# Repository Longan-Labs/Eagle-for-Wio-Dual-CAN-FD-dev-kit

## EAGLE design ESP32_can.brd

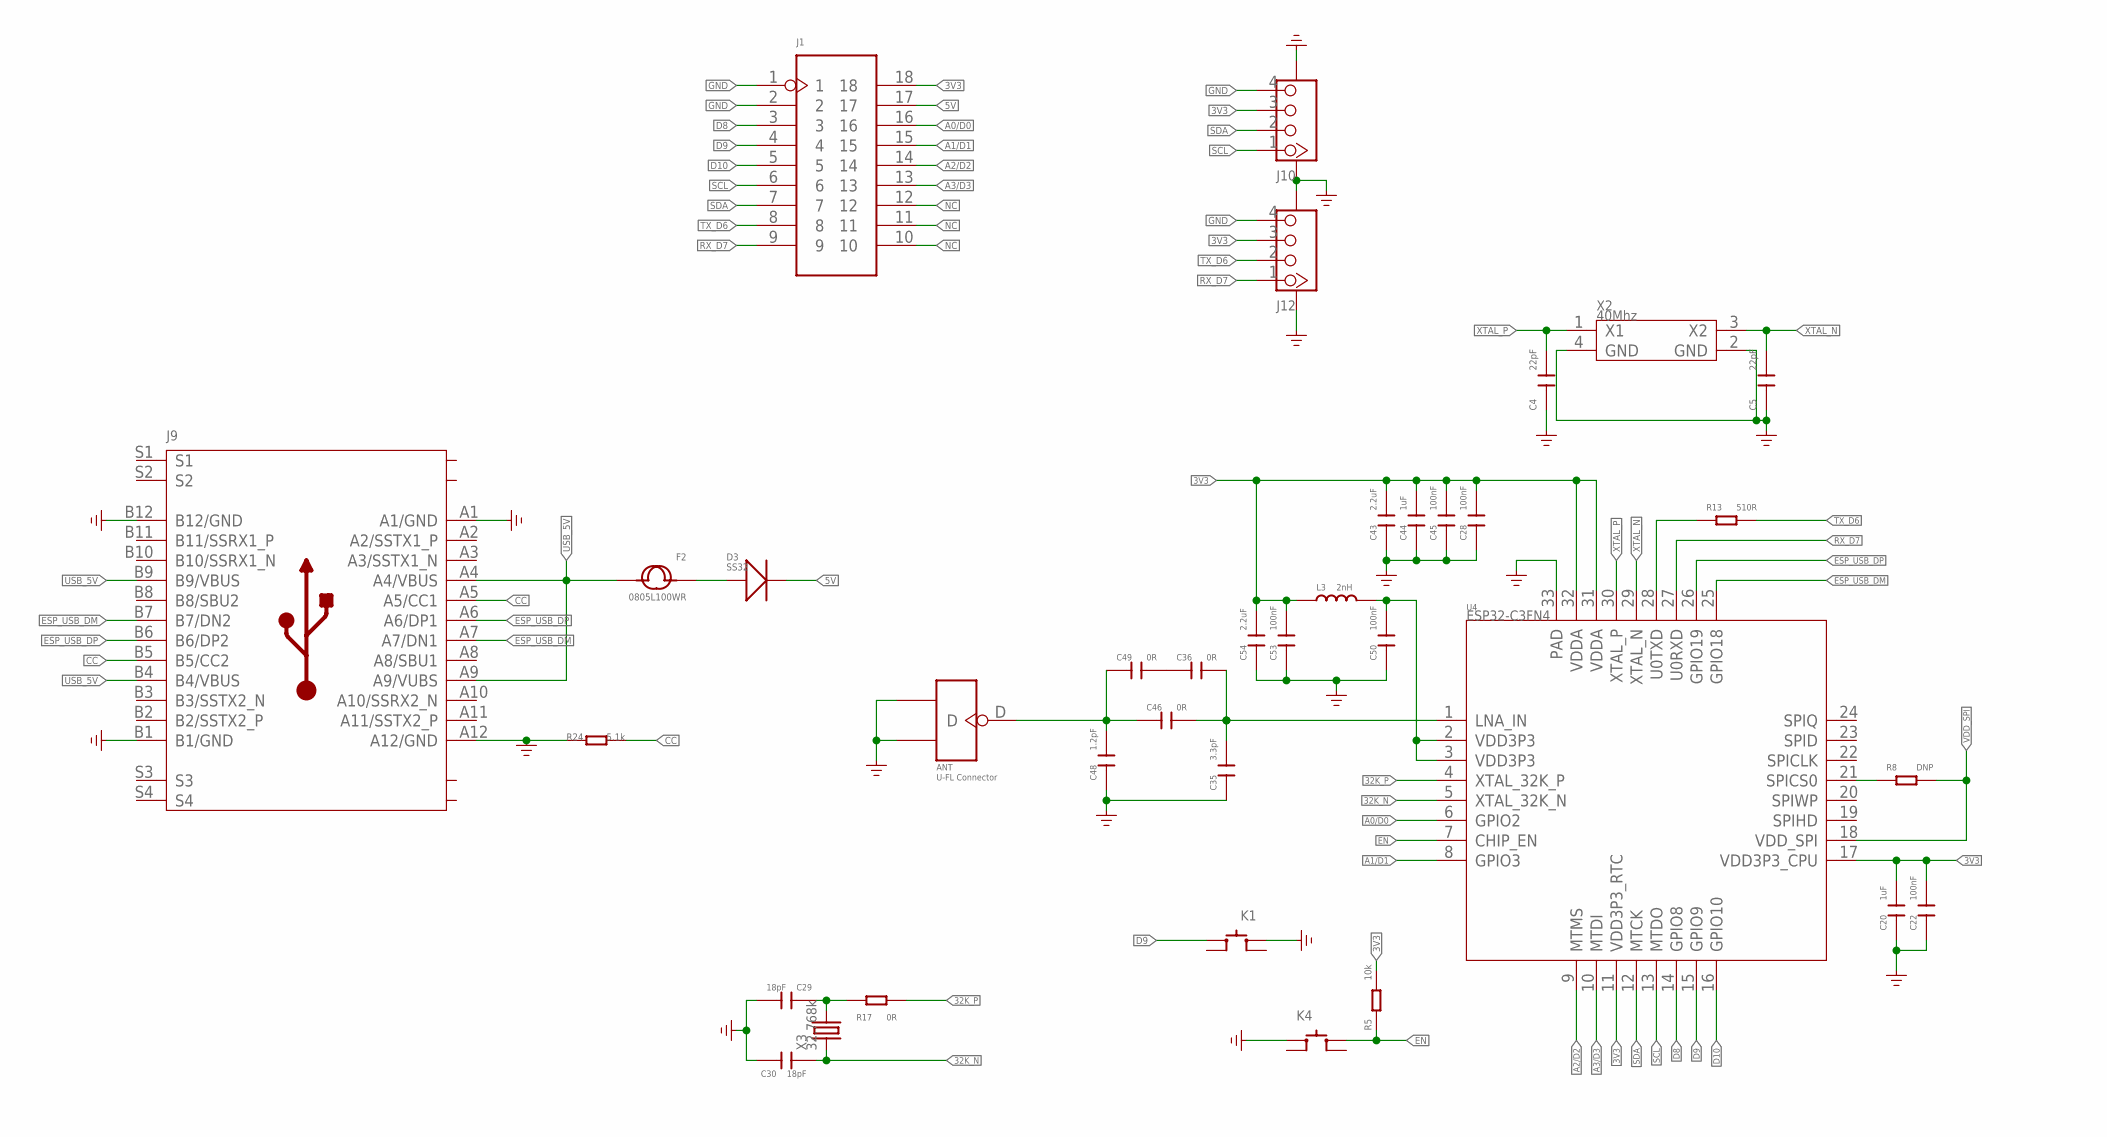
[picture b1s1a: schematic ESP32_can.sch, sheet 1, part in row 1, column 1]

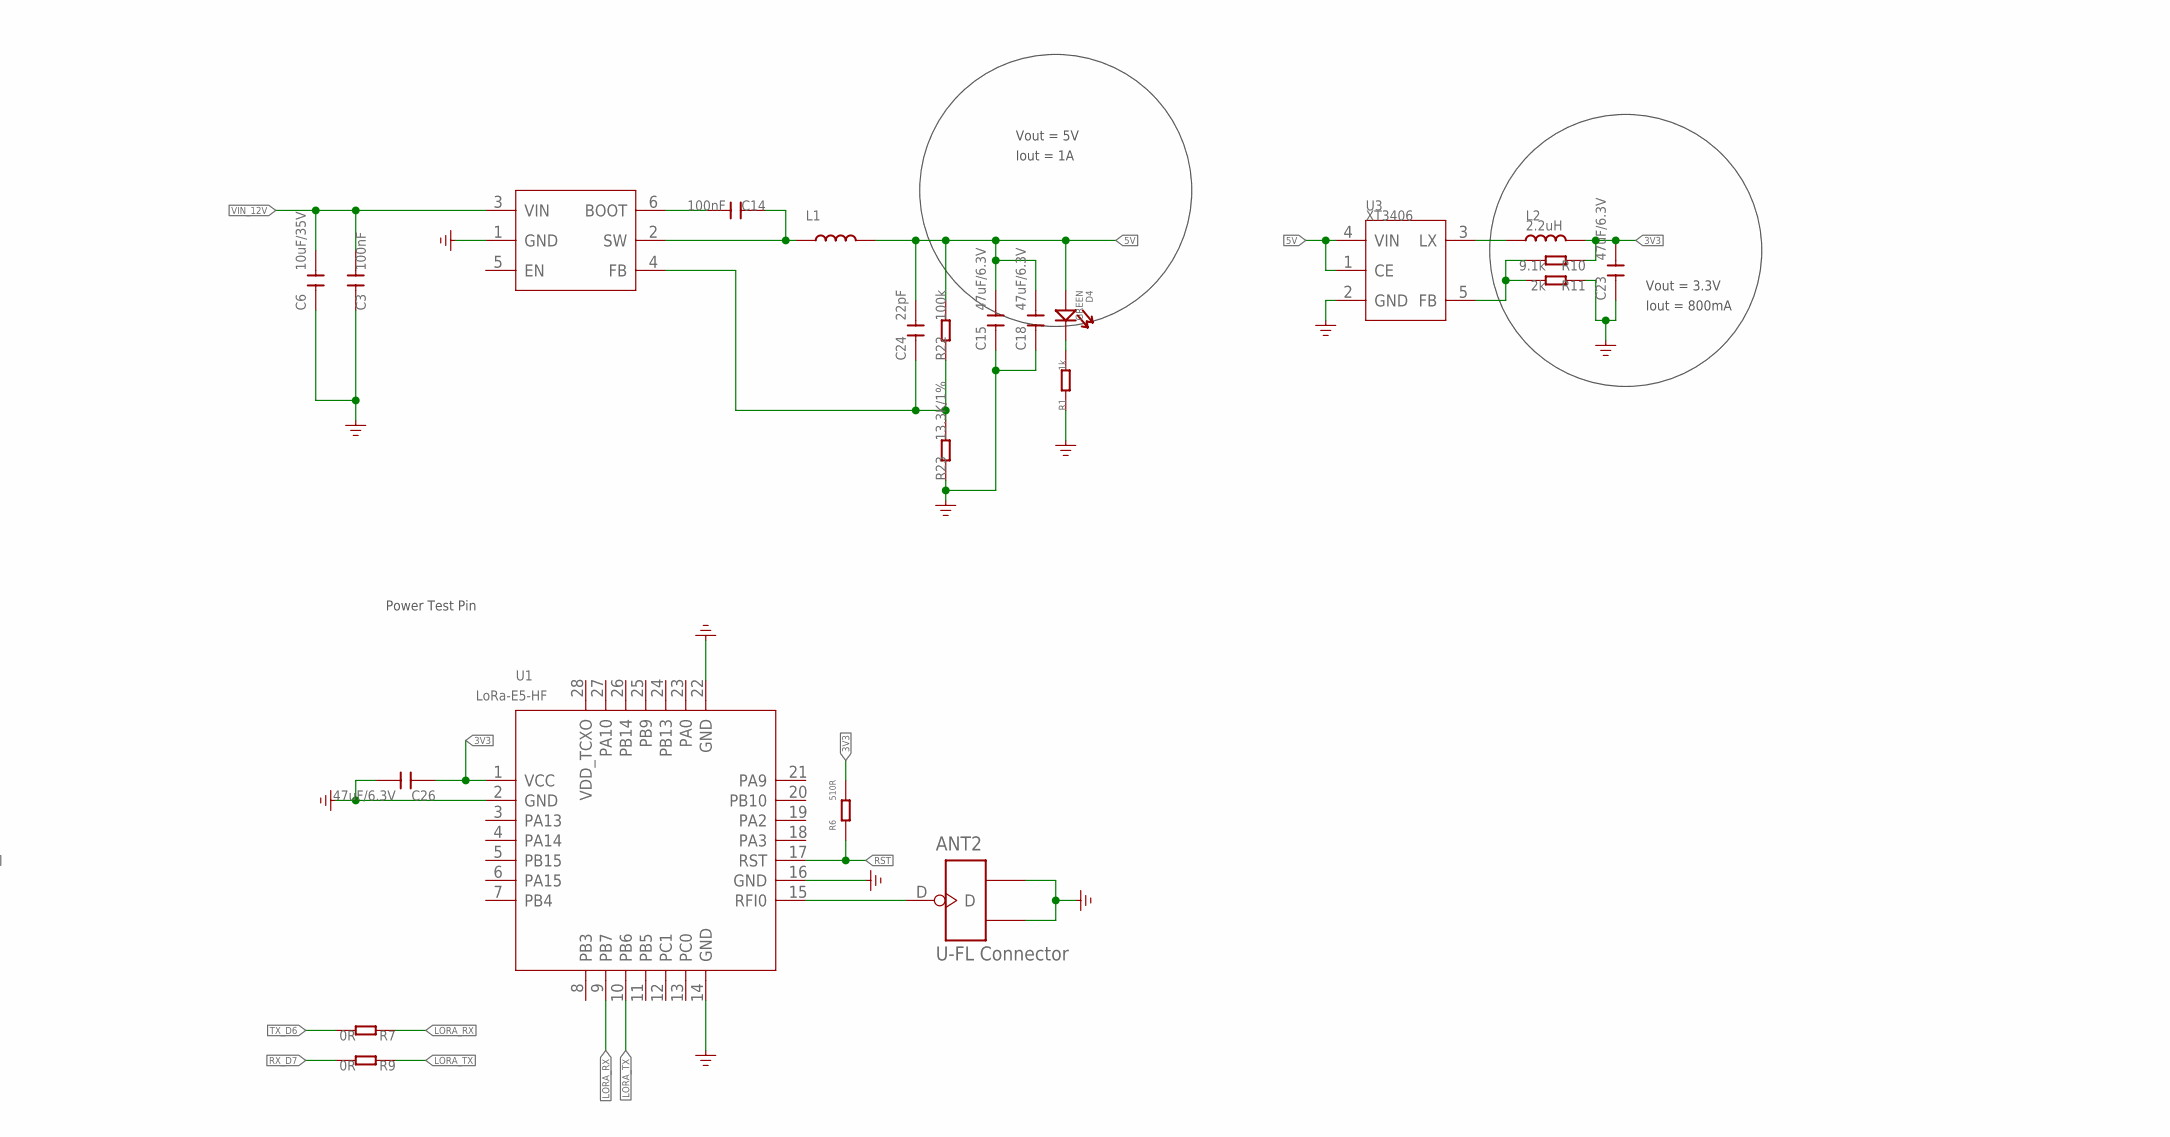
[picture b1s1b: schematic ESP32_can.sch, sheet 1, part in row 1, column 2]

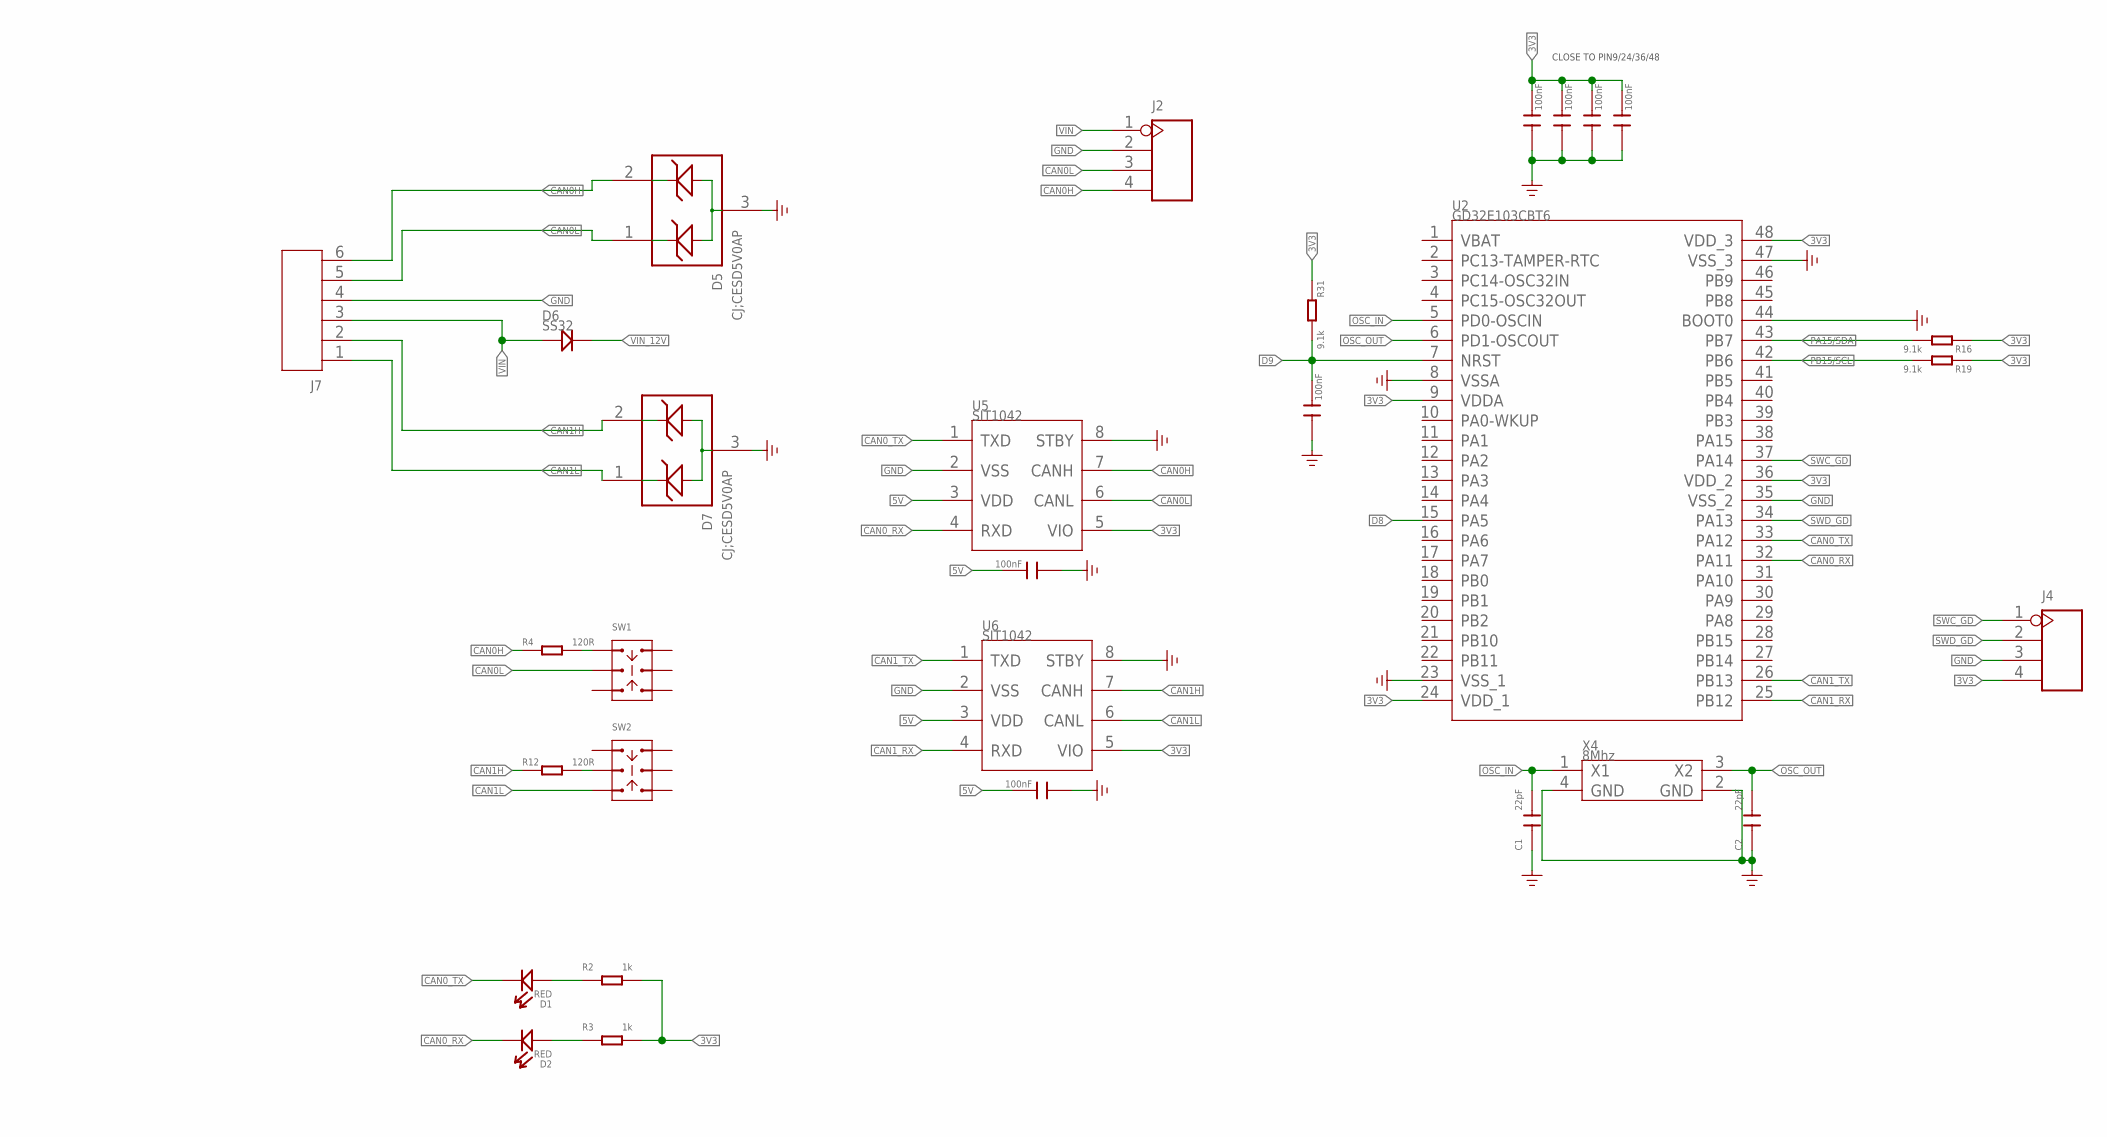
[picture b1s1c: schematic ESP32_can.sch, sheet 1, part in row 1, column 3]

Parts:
ANT, ANT2: U-FL Connector; U-FL3P-SMD-2.6X2.6X1.0MM
C1, C2, C4, C5, C24: 22pF; C0603
C3, C7, C8, C9, C10, C14, C16, C17, C19, C22, C28, C45, C50, C53: 100nF; C0603
C6: 10uF/35V; C1206
C15, C18, C23, C26: 47uF/6.3V; C0805
C20, C44: 1uF; C0603
C29, C30: 18pF; C0603
C35: 3.3pF; C0603
C36, C46, C49: 0R; C0603
C43, C54: 2.2uF; C0603
C48: 1.2pF; C0603
D1, D2: RED; LED-0603
D3: SS32; DO-214AC@2
D4: GREEN; LED-0603
D5, D7: CJ;CESD5V0AP; SOT-23
D6: SS32; DO-214AC
F2: 0805L100WR; F0805
J1: HEADER-2X9P-2.54; H2X9-2.54
J2: HEADER-4P-80/40MIL; H4-2.54-C80D40MIL
J4: HEADER-4P-65/35MIL; H4-2.54
J7: SCREW-TERMINAL-6P-5.0; H6-5.0-31.6X12.5X12MM
J9: USB-TYPE-C-90; TYPE-C-0.5-8.94X3.16X9.2MM
J10, J12: GROVE-CONNECTOR-SMD-320110030; HW4-SMD-2.0
K1, K4: BUTTON-4P-6.2X6.2; SW4-SMD-6.2X6.2MM
L1: INDUCTOR-SPD3D16-4R7M; L0420
L2: 2.2uH; L3030-TAIYO-YUDEN-NR3012
L3: 2nH; L0603
R1, R2, R3: 1k; R0603
R4, R12: 120R; R0603
R5: 10k; R0603
R6, R13: 510R; R0603
R7, R9, R17: 0R; R0603
R8: DNP; R0603
R10, R16, R19, R31: 9.1k; R0603
R11: 2k; R0603
R22: 100k; R0603
R23: 13.3K/1%; R0603
R24: 5.1k; R0603
SW1, SW2: SWITCH-2CH-6P-311010004; SW6-2.54-9.0X3.5X3.2+2.0MM
U1: LoRa-E5-HF; MOUDLE28P-1.25-12X12X2.5MM
U2: GD32E103CBT6; LQFP48
U3: XT3406; SOT-23-5
U4: ESP32-C3FN4; QFN32G-0.5-5X5MM
U5, U6: SIT1042; SOIC8-1.27-5X4MM
U9: PMIC-TPS54302; SOT-23-6
X2: 40Mhz; X4-SMD-3.2X2.5X0.7MM
X3: 32.768k; X2-SMD-1.6X1.0X0.5MM
X4: 8Mhz; X4-SMD-3.2X2.5X0.7MM

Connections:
3V3: C7.2, C9.2, C16.2, C17.2, C20.2, C22.2, C23.2, C26.1, C28.2, C43.2, C44.2, C45.2, C53.2, C54.2, J1.18, J4.4, J10.3, J12.3, L2.2, L3.1, R2.2, R3.2, R5.2, R6.1, R10.1, R16.1, R19.1, R31.1, U1.1 (VCC), U2.9 (VDDA), U2.24 (VDD_1), U2.36 (VDD_2), U2.48 (VDD_3), U4.11 (VDD3P3_RTC), U4.17 (VDD3P3_CPU), U4.31 (VDDA), U4.32 (VDDA), U5.5 (VIO), U6.5 (VIO)
5V: C8.2, C15.2, C18.2, C19.2, C24.2, D3.2 (-), D4.+, J1.17, L1.2, R22.2, U3.1 (CE), U3.4 (VIN), U5.3 (VDD), U6.3 (VDD)
32K_N: C30.1, U4.5 (XTAL_32K_N), X3.1
32K_P: R17.1, U4.4 (XTAL_32K_P)
A0/D0: J1.16, U4.6 (GPIO2)
A1/D1: J1.15, U4.8 (GPIO3)
A2/D2: J1.14, U4.9 (MTMS)
A3/D3: J1.13, U4.10 (MTDI)
CAN0H: D5.2, J2.4, J7.6, R4.1, U5.7 (CANH)
CAN0L: D5.1, J2.3, J7.5, SW1.COM1, U5.6 (CANL)
CAN0_RX: D2.-, U2.32 (PA11), U5.4 (RXD)
CAN0_TX: D1.-, U2.33 (PA12), U5.1 (TXD)
CAN1H: D7.2, J7.2, R12.1, U6.7 (CANH)
CAN1L: D7.1, J7.1, SW2.CH1B, U6.6 (CANL)
CAN1_RX: U2.25 (PB12), U6.4 (RXD)
CAN1_TX: U2.26 (PB13), U6.1 (TXD)
CC: J9.A5 (A5/CC1), J9.B5 (B5/CC2), R24.2
D8: J1.3, U2.15 (PA5), U4.14 (GPIO8)
D9: C10.2, J1.4, K1.2 (B0), R31.2, U2.7 (NRST), U4.15 (GPIO9)
D10: J1.5, U4.16 (GPIO10)
EN: K4.2 (B0), R5.1, U4.7 (CHIP_EN)
ESP_USB_DM: J9.A7 (A7/DN1), J9.B7 (B7/DN2), U4.25 (GPIO18)
ESP_USB_DP: J9.A6 (A6/DP1), J9.B6 (B6/DP2), U4.26 (GPIO19)
GND: ANT.GND1, ANT.GND2, ANT2.GND1, ANT2.GND2, C1.1, C2.1, C3.1, C4.1, C5.1, C6.1, C7.1, C8.1, C9.1, C10.1, C15.1, C16.1, C17.1, C18.1, C19.1, C20.1, C22.1, C23.1, C26.2, C28.1, C29.2, C30.2, C35.1, C43.1, C44.1, C45.1, C48.1, C50.1, C53.1, C54.1, D5.3, D7.3, J1.1, J1.2, J2.2, J4.3, J7.4, J9.A1 (A1/GND), J9.A12 (A12/GND), J9.B1 (B1/GND), J9.B12 (B12/GND), J10.4, J10.SS1, J10.SS2, J12.4, J12.SS1, J12.SS2, K1.1 (A0), K4.1 (A0), R1.1, R11.1, R23.1, R24.1, U1.2 (GND), U1.14 (GND), U1.16 (GND), U1.22 (GND), U2.8 (VSSA), U2.23 (VSS_1), U2.35 (VSS_2), U2.44 (BOOT0), U2.47 (VSS_3), U3.2 (GND), U4.33 (PAD), U5.2 (VSS), U5.8 (STBY), U6.2 (VSS), U6.8 (STBY), U9.1 (GND), X2.2 (GND), X2.4 (GND), X4.2 (GND), X4.4 (GND)
LORA_RX: R7.1, U1.9 (PB7)
LORA_TX: R9.1, U1.10 (PB6)
unnamed: D4.-, R1.2
unnamed: D1.+, R2.1
unnamed: C14.1, L1.1, U9.2 (SW)
unnamed: ANT2.D, U1.15 (RFI0)
unnamed: R4.2, SW1.CH1A
unnamed: R12.2, SW2.COM1
unnamed: L2.1, U3.3 (LX)
unnamed: D3.1 (+), F2.1
unnamed: R13.2, U4.28 (U0TXD)
unnamed: D2.+, R3.1
unnamed: R10.2, R11.2, U3.5 (FB)
unnamed: R8.1, U4.21 (SPICS0)
unnamed: C29.1, R17.2, X3.2
unnamed: C35.2, C36.1, C46.2, U4.1 (LNA_IN)
unnamed: C36.2, C49.1
unnamed: C14.2, U9.6 (BOOT)
unnamed: ANT.D, C46.1, C48.2, C49.2
unnamed: C24.1, R22.1, R23.2, U9.4 (FB)
unnamed: C50.2, L3.2, U4.2 (VDD3P3), U4.3 (VDD3P3)
NC: J1.10, J1.11, J1.12
OSC_IN: C1.2, U2.5 (PD0-OSCIN), X4.1 (X1)
OSC_OUT: C2.2, U2.6 (PD1-OSCOUT), X4.3 (X2)
PA15/SDA: R16.2, U2.43 (PB7)
PB15/SCL: R19.2, U2.42 (PB6)
RST: R6.2, U1.17 (RST)
RX_D7: J1.9, J12.1, R9.2, U4.27 (U0RXD)
SCL: J1.6, J10.1, U4.13 (MTDO)
SDA: J1.7, J10.2, U4.12 (MTCK)
SWC_GD: J4.1, U2.37 (PA14)
SWD_GD: J4.2, U2.34 (PA13)
TX_D6: J1.8, J12.2, R7.2, R13.1
USB_5V: F2.2, J9.A4 (A4/VBUS), J9.A9 (A9/VUBS), J9.B4 (B4/VBUS), J9.B9 (B9/VBUS)
VDD_SPI: R8.2, U4.18 (VDD_SPI)
VIN: D6.1 (+), J2.1, J7.3
VIN_12V: C3.2, C6.2, D6.2 (-), U9.3 (VIN)
XTAL_N: C5.2, U4.29 (XTAL_N), X2.3 (X2)
XTAL_P: C4.2, U4.30 (XTAL_P), X2.1 (X1)

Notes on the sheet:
Power Test Pin
Vout = 5V
Iout = 1A
CLOSE TO PIN9/24/36/48
Vout = 3.3V
Iout = 800mA

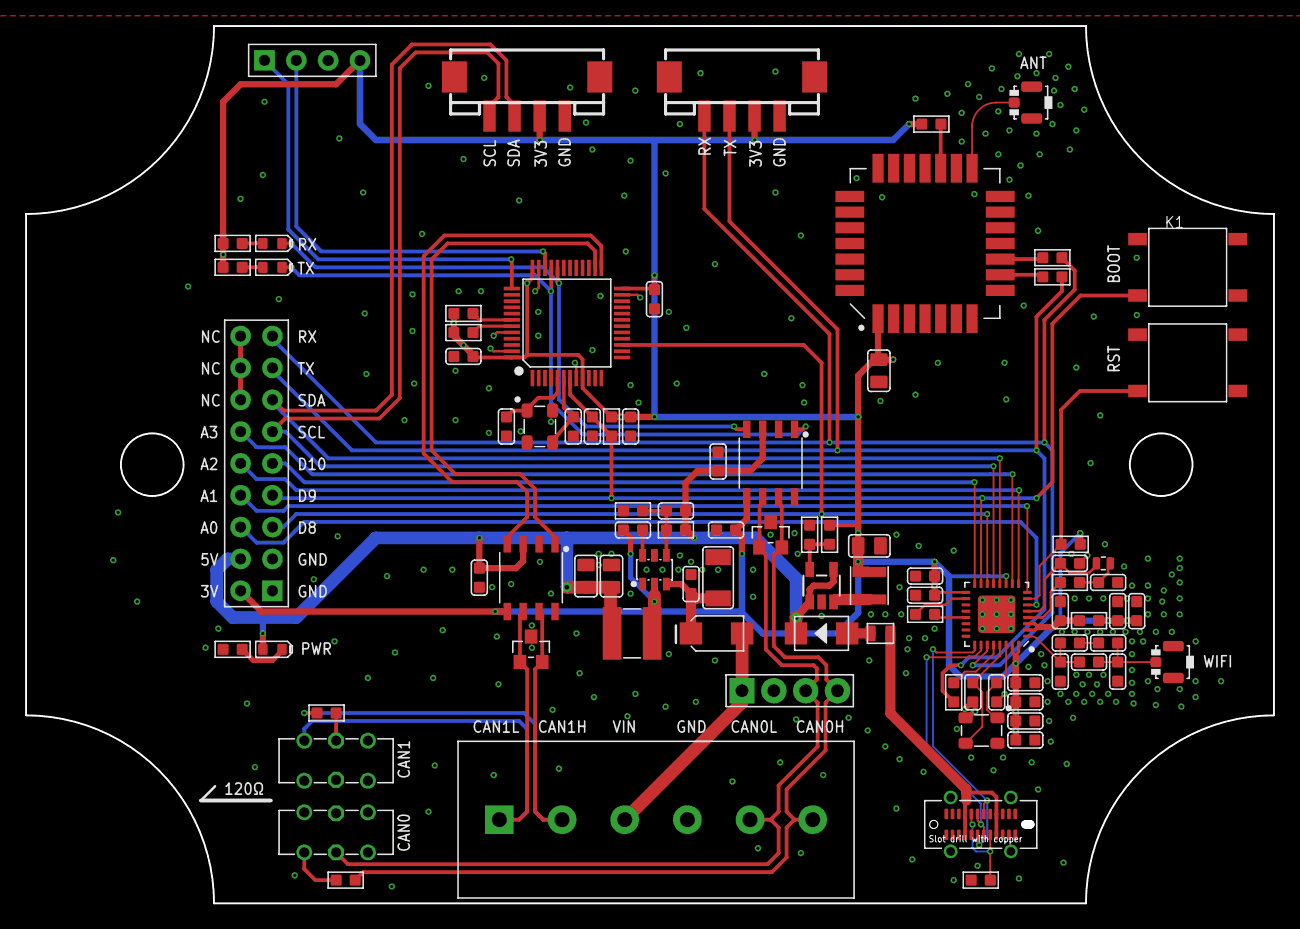
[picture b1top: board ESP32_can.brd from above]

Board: 2 copper layers, 99.1 x 69.5 mm, 89 parts (0 on the bottom side), 63 nets.
